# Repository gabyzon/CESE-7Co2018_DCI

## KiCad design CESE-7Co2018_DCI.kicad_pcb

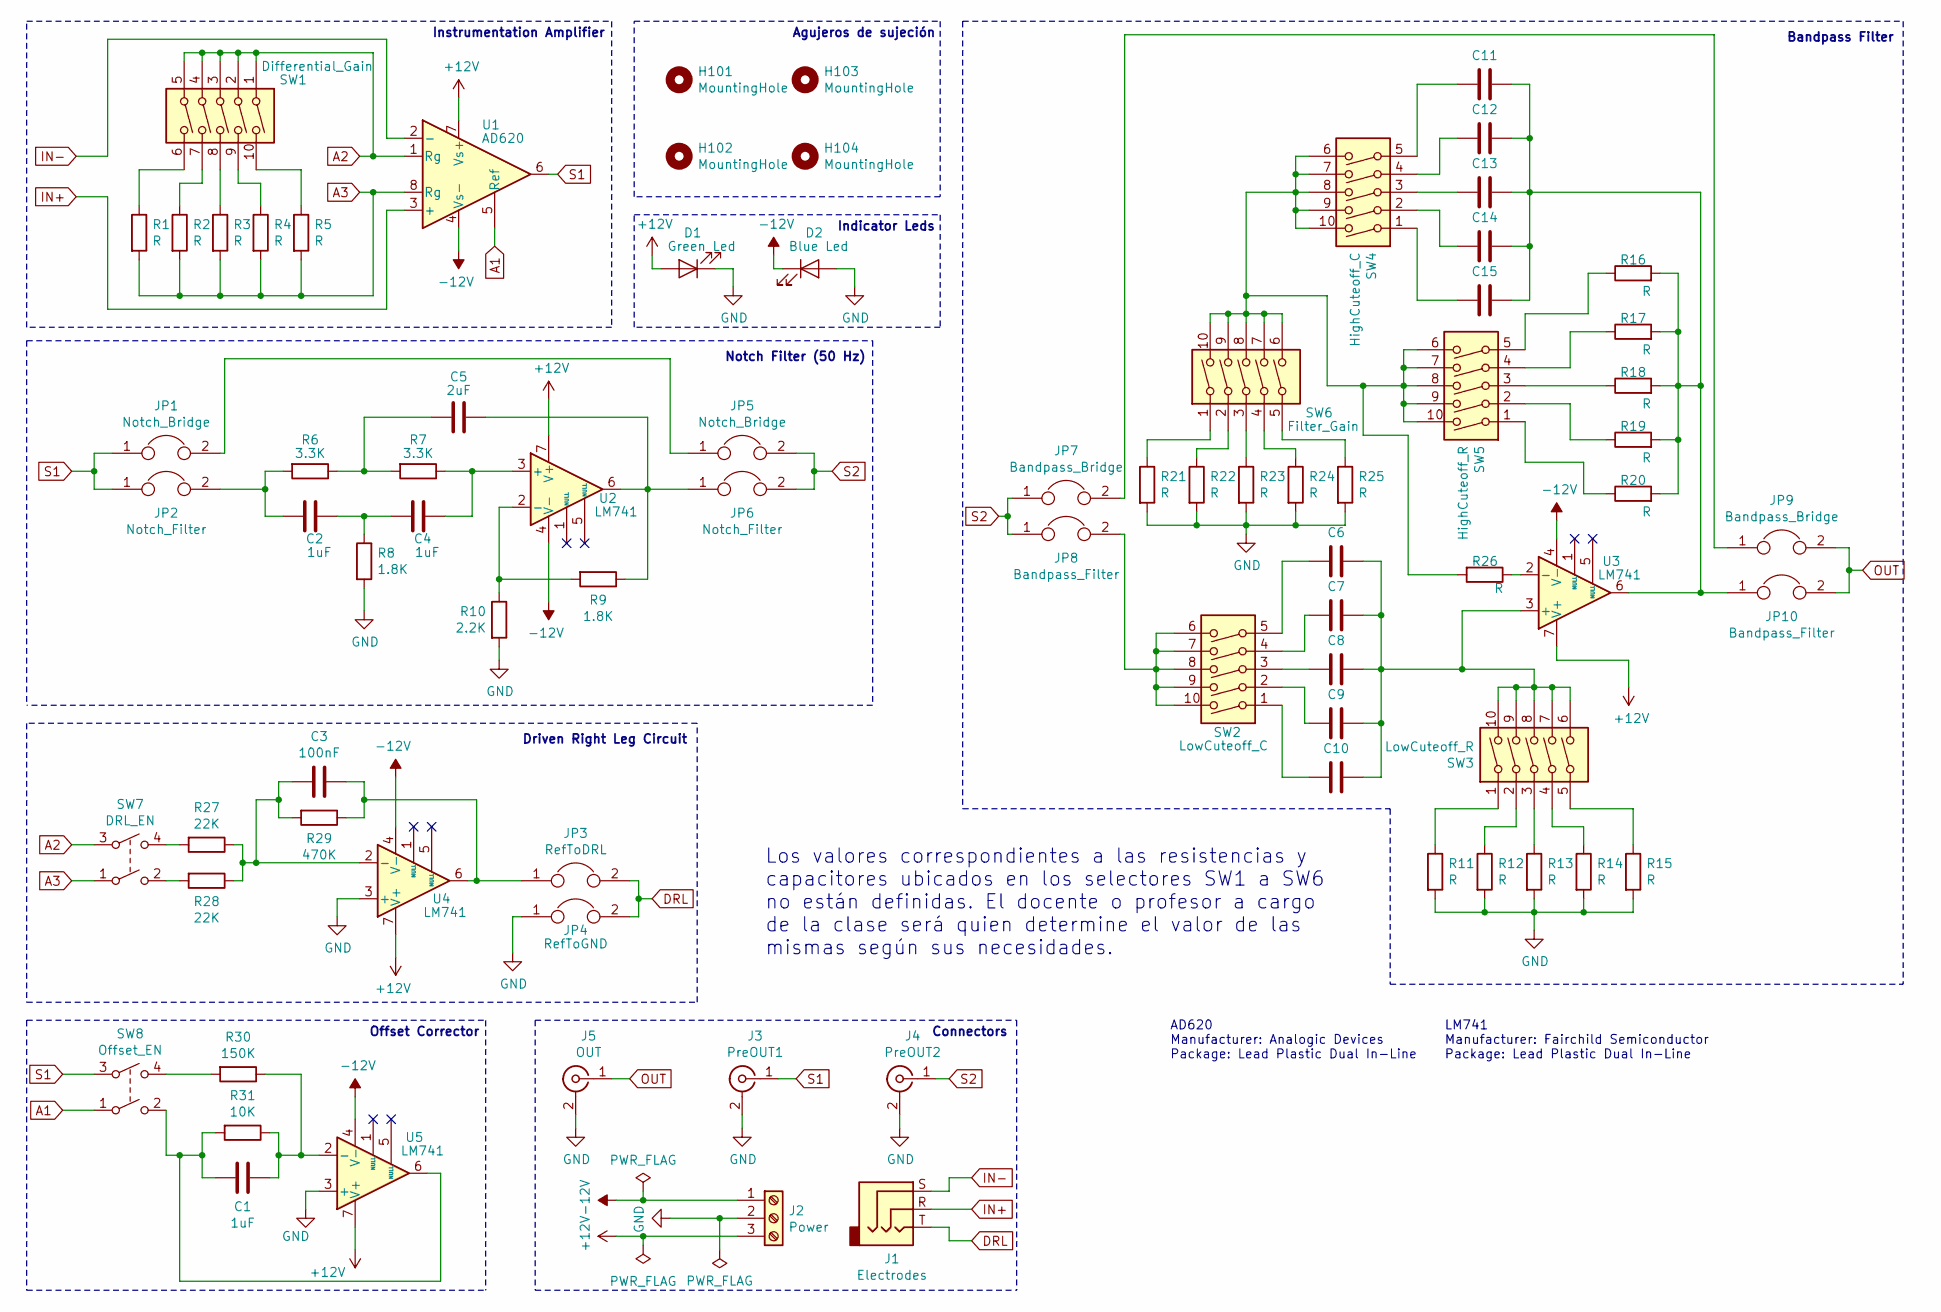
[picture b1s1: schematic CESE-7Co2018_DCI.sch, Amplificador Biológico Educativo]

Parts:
C1, C2, C4: 1uF; C_Disc_D6.0mm_W2.5mm_P5.00mm
C3: 100nF; C_Disc_D6.0mm_W2.5mm_P5.00mm
C5: 2uF; C_Disc_D6.0mm_W2.5mm_P5.00mm
C6, C7, C8, C9, C10, C11, C12, C13, C14, C15: C; C_Disc_D6.0mm_W2.5mm_P5.00mm
D1: Green Led; LED_D5.0mm
D2: Blue Led; LED_D5.0mm
H101, H102, H103, H104: MountingHole; MountingHole_3.7mm_Pad
J1: Electrodes; Jack_3.5mm_CUI_SJ1-3533NG_Horizontal
J2: Power; TerminalBlock_MetzConnect_Type094_RT03503HBLU_1x03_P5.00mm_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
J3: PreOUT1; BNC_Amphenol_B6252HB-NPP3G-50_Horizontal
J4: PreOUT2; BNC_Amphenol_B6252HB-NPP3G-50_Horizontal
J5: OUT; BNC_Amphenol_B6252HB-NPP3G-50_Horizontal
JP1, JP5: Notch_Bridge; PinHeader_1x02_P2.54mm_Vertical
JP2, JP6: Notch_Filter; PinHeader_1x02_P2.54mm_Vertical
JP3: RefToDRL; PinHeader_1x02_P2.54mm_Vertical
JP4: RefToGND; PinHeader_1x02_P2.54mm_Vertical
JP7, JP9: Bandpass_Bridge; PinHeader_1x02_P2.54mm_Vertical
JP8, JP10: Bandpass_Filter; PinHeader_1x02_P2.54mm_Vertical
R1, R2, R3, R4, R5, R11, R12, R13, R14, R15, R16, R17, R18, R19, R20, R21, R22, R23, R24, R25, R26: R; R_Axial_DIN0207_L6.3mm_D2.5mm_P7.62mm_Horizontal
R6, R7: 3.3K; R_Axial_DIN0207_L6.3mm_D2.5mm_P7.62mm_Horizontal
R8, R9: 1.8K; R_Axial_DIN0207_L6.3mm_D2.5mm_P7.62mm_Horizontal
R10: 2.2K; R_Axial_DIN0207_L6.3mm_D2.5mm_P7.62mm_Horizontal
R27, R28: 22K; R_Axial_DIN0207_L6.3mm_D2.5mm_P7.62mm_Horizontal
R29: 470K; R_Axial_DIN0207_L6.3mm_D2.5mm_P7.62mm_Horizontal
R30: 150K; R_Axial_DIN0207_L6.3mm_D2.5mm_P7.62mm_Horizontal
R31: 10K; R_Axial_DIN0207_L6.3mm_D2.5mm_P7.62mm_Horizontal
SW1: Differential_Gain; SW_DIP_SPSTx05_Slide_9.78x14.88mm_W7.62mm_P2.54mm
SW2: LowCuteoff_C; SW_DIP_SPSTx05_Slide_9.78x14.88mm_W7.62mm_P2.54mm
SW3: LowCuteoff_R; SW_DIP_SPSTx05_Slide_9.78x14.88mm_W7.62mm_P2.54mm
SW4: HighCuteoff_C; SW_DIP_SPSTx05_Slide_9.78x14.88mm_W7.62mm_P2.54mm
SW5: HighCuteoff_R; SW_DIP_SPSTx05_Slide_9.78x14.88mm_W7.62mm_P2.54mm
SW6: Filter_Gain; SW_DIP_SPSTx05_Slide_9.78x14.88mm_W7.62mm_P2.54mm
SW7: DRL_EN; SW_DIP_SPSTx02_Slide_9.78x7.26mm_W7.62mm_P2.54mm
SW8: Offset_EN; SW_DIP_SPSTx02_Slide_9.78x7.26mm_W7.62mm_P2.54mm
U1: AD620; DIP-8_W7.62mm_Socket
U2, U3, U4, U5: LM741; DIP-8_W7.62mm_Socket

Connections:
+12V: D1.2 (A), J2.3, U1.7 (Vs+), U2.7 (V+), U3.7 (V+), U4.7 (V+), U5.7 (V+)
-12V: D2.1 (K), J2.1, U1.4 (Vs-), U2.4 (V-), U3.4 (V-), U4.4 (V-), U5.4 (V-)
A1: SW8.1, U1.5 (Ref)
A2: SW1.1, SW1.2, SW1.3, SW1.4, SW1.5, SW7.3, U1.1 (Rg)
A3: R1.2, R2.2, R3.2, R4.2, R5.2, SW7.1, U1.8 (Rg)
DRL: J1.T, JP3.2, JP4.2
GND: D1.1 (K), D2.2 (A), J2.2, J3.2 (Ext), J4.2 (Ext), J5.2 (Ext), JP4.1, R8.2, R10.2, R11.2, R12.2, R13.2, R14.2, R15.2, R21.2, R22.2, R23.2, R24.2, R25.2, U4.3 (+), U5.3 (+)
IN+: J1.R, U1.3 (+)
IN-: J1.S, U1.2 (-)
unnamed: C1.1, R30.1, R31.1, U5.2 (-)
unnamed: C1.2, R31.2, SW8.2, U5.6
unnamed: C2.1, C4.2, R8.1
unnamed: C2.2, JP2.2, R6.2
unnamed: C3.1, JP3.1, R29.1, U4.6
unnamed: C3.2, R27.1, R28.1, R29.2, U4.2 (-)
unnamed: C4.1, R7.1, U2.3 (+)
unnamed: C5.1, JP6.1, R9.1, U2.6
unnamed: C5.2, R6.1, R7.2
unnamed: C6.2, SW2.5
unnamed: C7.2, SW2.4
unnamed: C8.2, SW2.3
unnamed: C9.2, SW2.2
unnamed: C6.1, C7.1, C8.1, C9.1, C10.1, SW3.6, SW3.7, SW3.8, SW3.9, SW3.10, U3.3 (+)
unnamed: C10.2, SW2.1
unnamed: C11.1, C12.1, C13.1, C14.1, C15.1, JP10.1, R16.2, R17.2, R18.2, R19.2, R20.2, U3.6
unnamed: C11.2, SW4.5
unnamed: C12.2, SW4.4
unnamed: C13.2, SW4.3
unnamed: C14.2, SW4.2
unnamed: C15.2, SW4.1
unnamed: JP1.2, JP5.1
unnamed: JP7.2, JP9.1
unnamed: JP8.2, SW2.6, SW2.7, SW2.8, SW2.9, SW2.10
unnamed: R1.1, SW1.6
unnamed: R2.1, SW1.7
unnamed: R3.1, SW1.8
unnamed: R4.1, SW1.9
unnamed: R5.1, SW1.10
unnamed: R9.2, R10.1, U2.2 (-)
unnamed: R11.1, SW3.1
unnamed: R12.1, SW3.2
unnamed: R13.1, SW3.3
unnamed: R14.1, SW3.4
unnamed: R15.1, SW3.5
unnamed: R16.1, SW5.5
unnamed: R17.1, SW5.4
unnamed: R18.1, SW5.3
unnamed: R19.1, SW5.2
unnamed: R20.1, SW5.1
unnamed: R21.1, SW6.1
unnamed: R22.1, SW6.2
unnamed: R23.1, SW6.3
unnamed: R24.1, SW6.4
unnamed: R25.1, SW6.5
unnamed: R26.1, U3.2 (-)
unnamed: R26.2, SW4.6, SW4.7, SW4.8, SW4.9, SW4.10, SW5.6, SW5.7, SW5.8, SW5.9, SW5.10, SW6.6, SW6.7, SW6.8, SW6.9, SW6.10
unnamed: R27.2, SW7.4
unnamed: R28.2, SW7.2
unnamed: R30.2, SW8.4
OUT: J5.1 (In), JP9.2, JP10.2
S1: J3.1 (In), JP1.1, JP2.1, SW8.3, U1.6
S2: J4.1 (In), JP5.2, JP6.2, JP7.1, JP8.1

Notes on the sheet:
Instrumentation Amplifier
Notch Filter (50 Hz)
Driven Right Leg Circuit
Offset Corrector
Bandpass Filter
Connectors
Agujeros de sujeción
Los valores correspondientes a las resistencias y capacitores ubicados en los selectores SW1 a SW6 no están definidas. El docente o profesor a cargo de la clase será quien determine el valor de las mismas según sus necesidades.
Indicator Leds
AD620 Manufacturer: Analogic Devices Package: Lead Plastic Dual In-Line
LM741 Manufacturer: Fairchild Semiconductor Package: Lead Plastic Dual In-Line

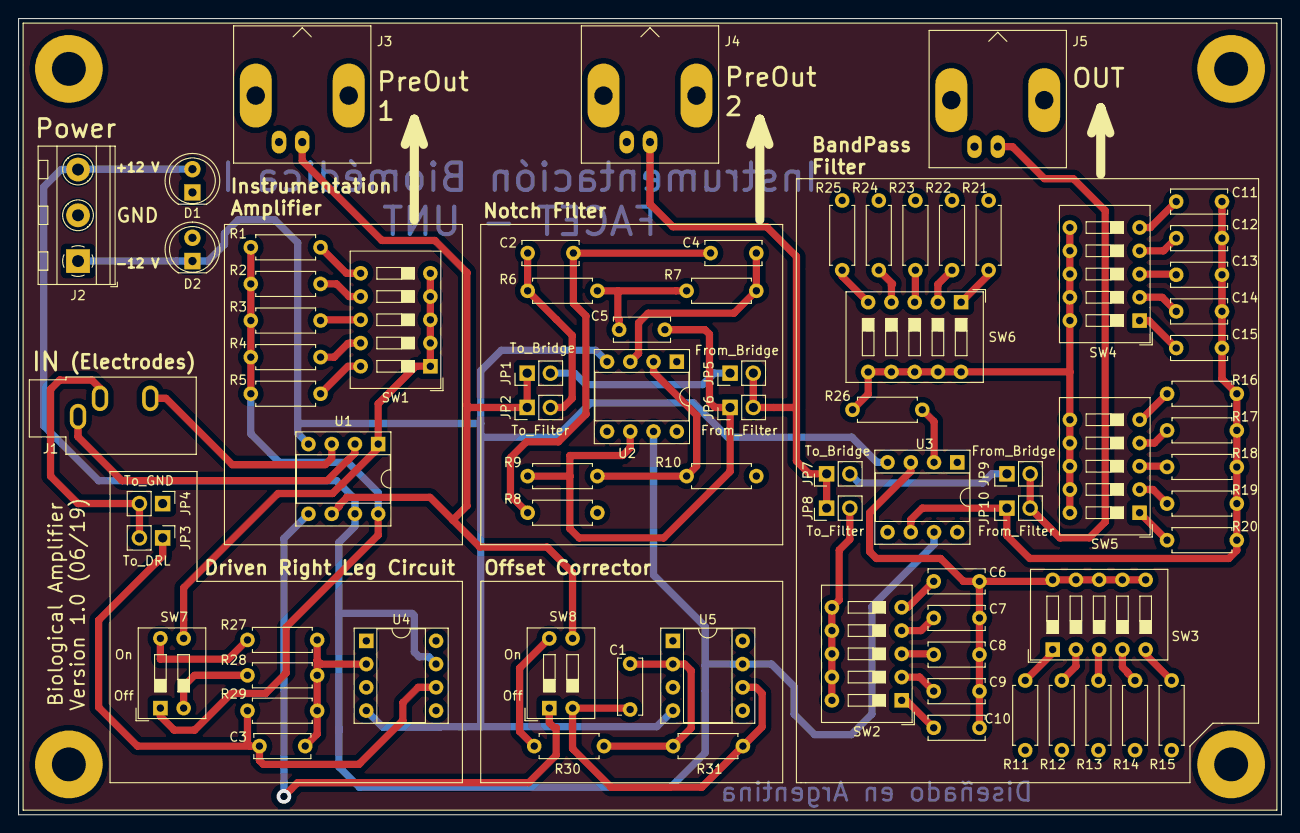
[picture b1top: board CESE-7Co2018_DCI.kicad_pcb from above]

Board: 2 copper layers, 138.0 x 87.0 mm, 80 parts (0 on the bottom side), 62 nets.

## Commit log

2019-06-13 Esquematico Completo
2019-06-17 Correcciones de la primera revision de Lucianna FA
2019-06-18 PCB Completo
2019-06-27 Con todas las correcciones recomendadas

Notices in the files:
CESE-7Co2018_DCI.kicad_pcb:
Licencia Creative Commons Attributions Share-Alike 4.0
